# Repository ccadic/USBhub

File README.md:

# USBhub
Small minimalistic 5V hub for powering miniminer. No USB D+ and D-

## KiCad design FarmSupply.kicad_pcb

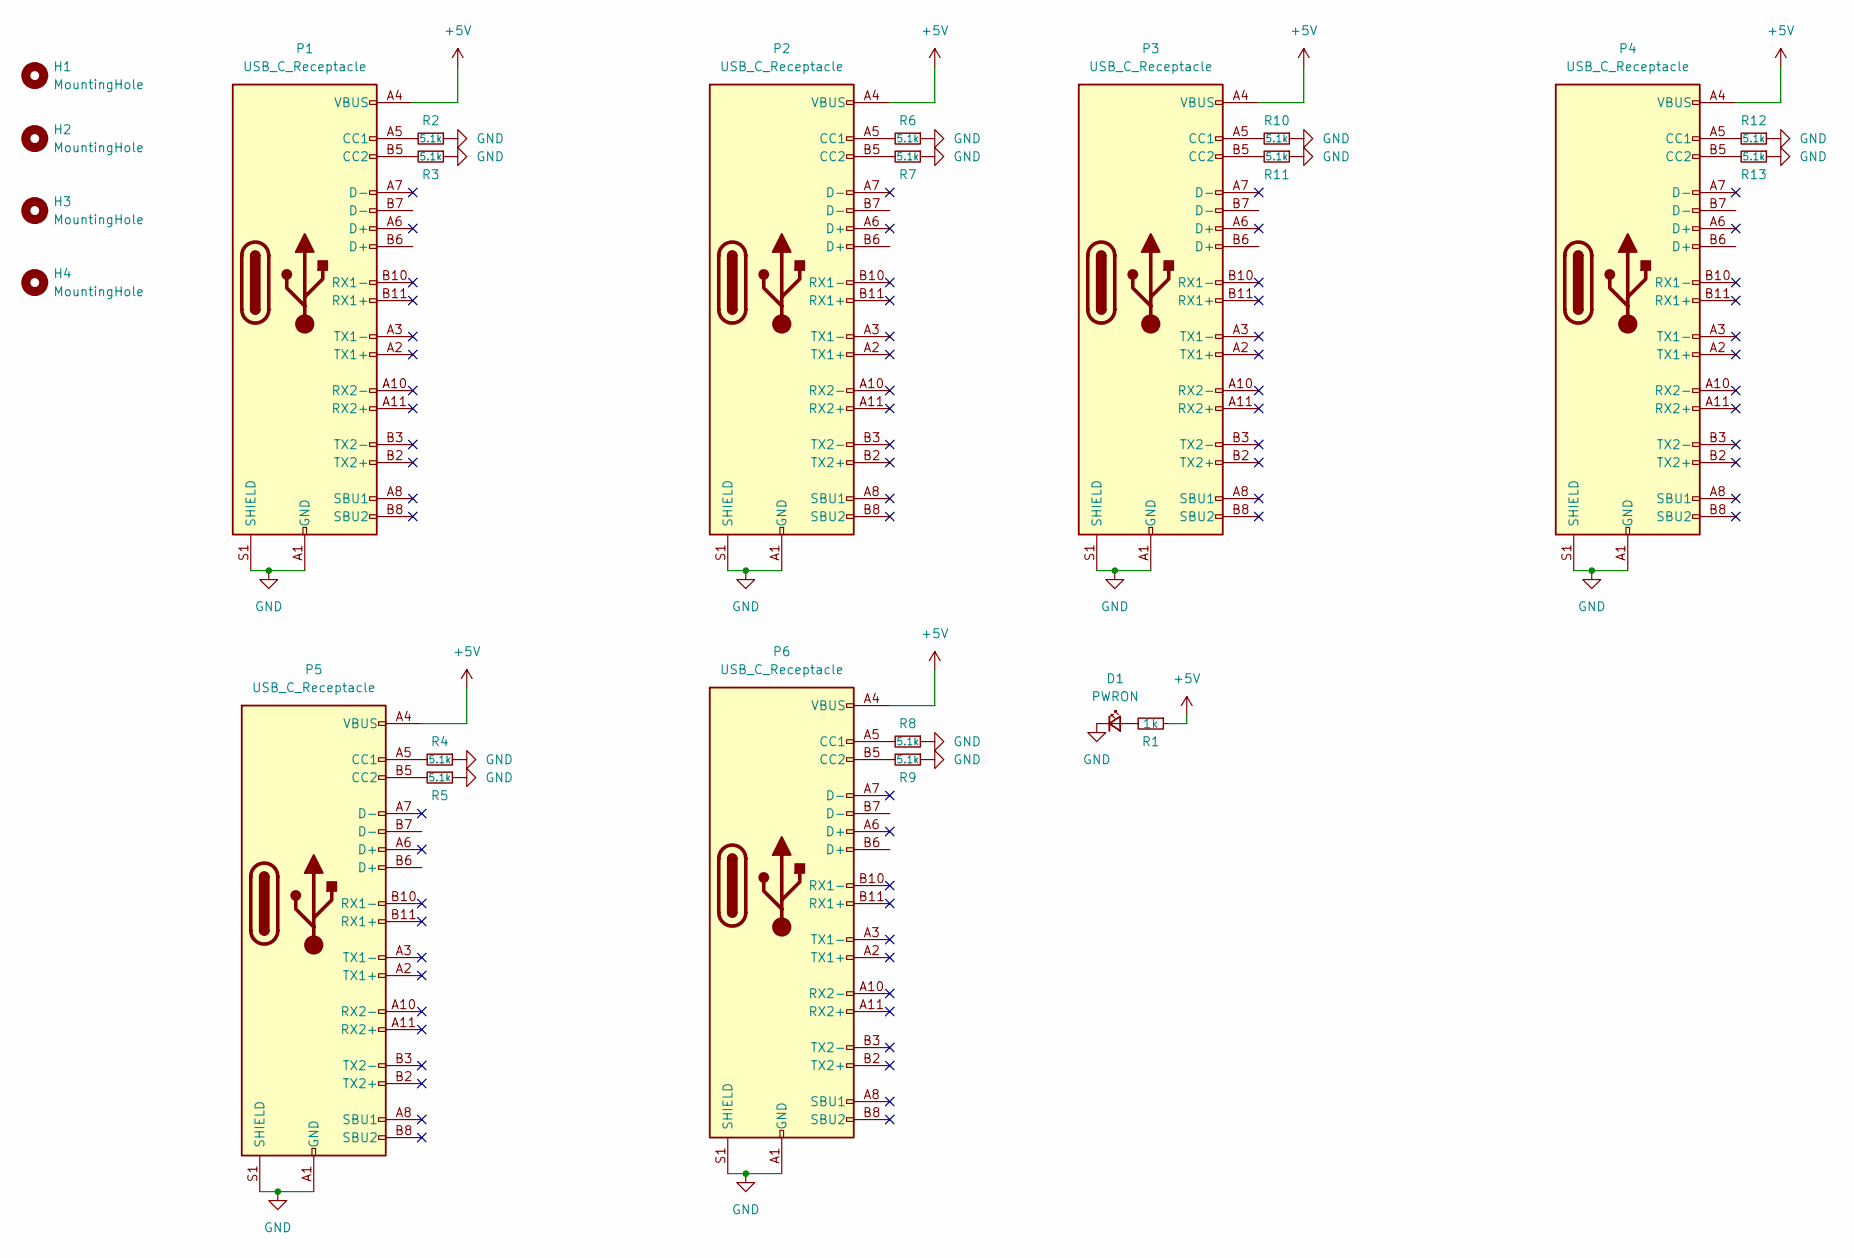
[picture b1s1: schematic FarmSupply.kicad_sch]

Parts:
D1: PWRON; LED_0805_2012Metric
H1, H2, H3, H4: MountingHole; MountingHole_3.2mm_M3
P1, P2, P3, P4, P5, P6: USB_C_Receptacle; GT-USB-7010
R1: 1k; R_0805_2012Metric
R2, R3, R4, R5, R6, R7, R8, R9, R10, R11, R12, R13: 5.1k; R_0805_2012Metric

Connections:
+5V: P1.A4 (VBUS), P1.A9 (VBUS), P1.B4 (VBUS), P1.B9 (VBUS), P2.A4 (VBUS), P2.A9 (VBUS), P2.B4 (VBUS), P2.B9 (VBUS), P3.A4 (VBUS), P3.A9 (VBUS), P3.B4 (VBUS), P3.B9 (VBUS), P4.A4 (VBUS), P4.A9 (VBUS), P4.B4 (VBUS), P4.B9 (VBUS), P5.A4 (VBUS), P5.A9 (VBUS), P5.B4 (VBUS), P5.B9 (VBUS), P6.A4 (VBUS), P6.A9 (VBUS), P6.B4 (VBUS), P6.B9 (VBUS), R1.1
GND: D1.1 (K), P1.A1 (GND), P1.A12 (GND), P1.B1 (GND), P1.B12 (GND), P1.S1 (SHIELD), P2.A1 (GND), P2.A12 (GND), P2.B1 (GND), P2.B12 (GND), P2.S1 (SHIELD), P3.A1 (GND), P3.A12 (GND), P3.B1 (GND), P3.B12 (GND), P3.S1 (SHIELD), P4.A1 (GND), P4.A12 (GND), P4.B1 (GND), P4.B12 (GND), P4.S1 (SHIELD), P5.A1 (GND), P5.A12 (GND), P5.B1 (GND), P5.B12 (GND), P5.S1 (SHIELD), P6.A1 (GND), P6.A12 (GND), P6.B1 (GND), P6.B12 (GND), P6.S1 (SHIELD), R2.1, R3.1, R4.1, R5.1, R6.1, R7.1, R8.1, R9.1, R10.1, R11.1, R12.1, R13.1
unnamed: D1.2 (A), R1.2
unnamed: P1.A5 (CC1), R2.2
unnamed: P1.B5 (CC2), R3.2
unnamed: P2.A5 (CC1), R6.2
unnamed: P2.B5 (CC2), R7.2
unnamed: P3.A5 (CC1), R10.2
unnamed: P3.B5 (CC2), R11.2
unnamed: P4.A5 (CC1), R12.2
unnamed: P4.B5 (CC2), R13.2
unnamed: P5.A5 (CC1), R4.2
unnamed: P5.B5 (CC2), R5.2
unnamed: P6.A5 (CC1), R8.2
unnamed: P6.B5 (CC2), R9.2

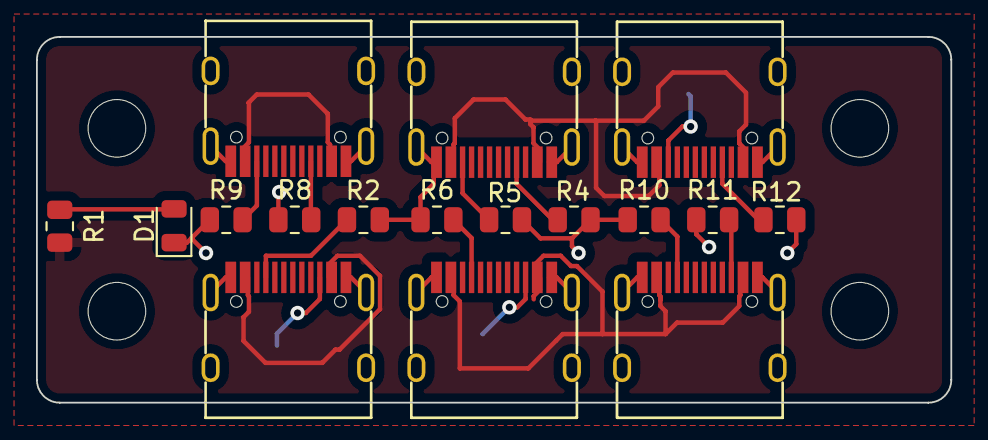
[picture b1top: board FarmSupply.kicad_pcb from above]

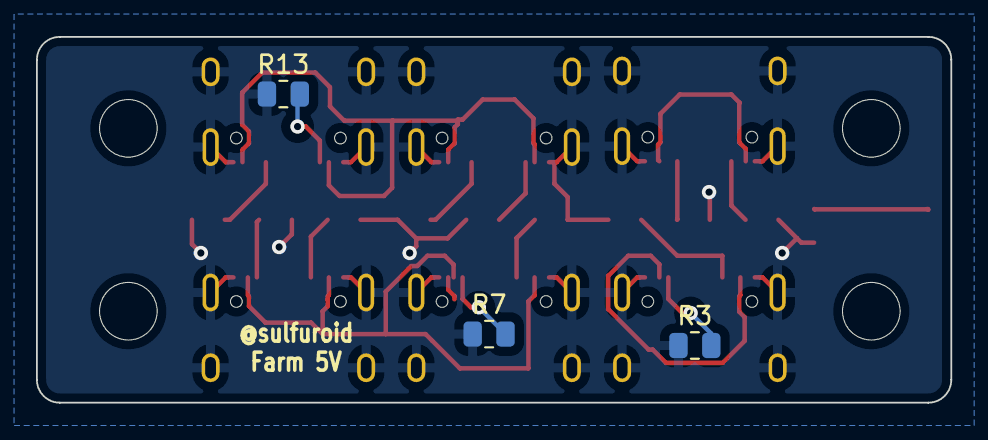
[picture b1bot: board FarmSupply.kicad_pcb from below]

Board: 2 copper layers, 50.8 x 20.3 mm, 24 parts (3 on the bottom side), 15 nets.
